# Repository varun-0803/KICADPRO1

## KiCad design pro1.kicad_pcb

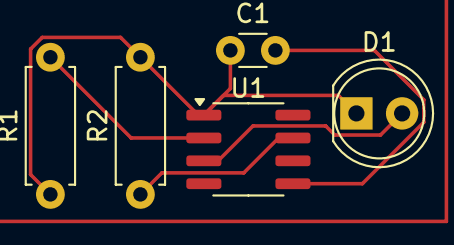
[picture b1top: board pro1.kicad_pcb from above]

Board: 2 copper layers, 5 parts (0 on the bottom side), 5 nets.

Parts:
C1: C; C_Disc_D3.0mm_W1.6mm_P2.50mm
D1: LED; LED_D5.0mm
R1, R2: R; R_Axial_DIN0207_L6.3mm_D2.5mm_P7.62mm_Horizontal
U1: LM555xM; SOIC-8_3.9x4.9mm_P1.27mm

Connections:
GND: C1.1, D1.1 (K), R1.1, R2.2, U1.1 (GND)
unnamed: D1.2 (A), U1.3 (Q)
unnamed: C1.2, U1.5 (CV)
unnamed: R2.1, U1.7 (DIS)
unnamed: R1.2, U1.2 (TR)

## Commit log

2025-06-16 Add KiCad project files
